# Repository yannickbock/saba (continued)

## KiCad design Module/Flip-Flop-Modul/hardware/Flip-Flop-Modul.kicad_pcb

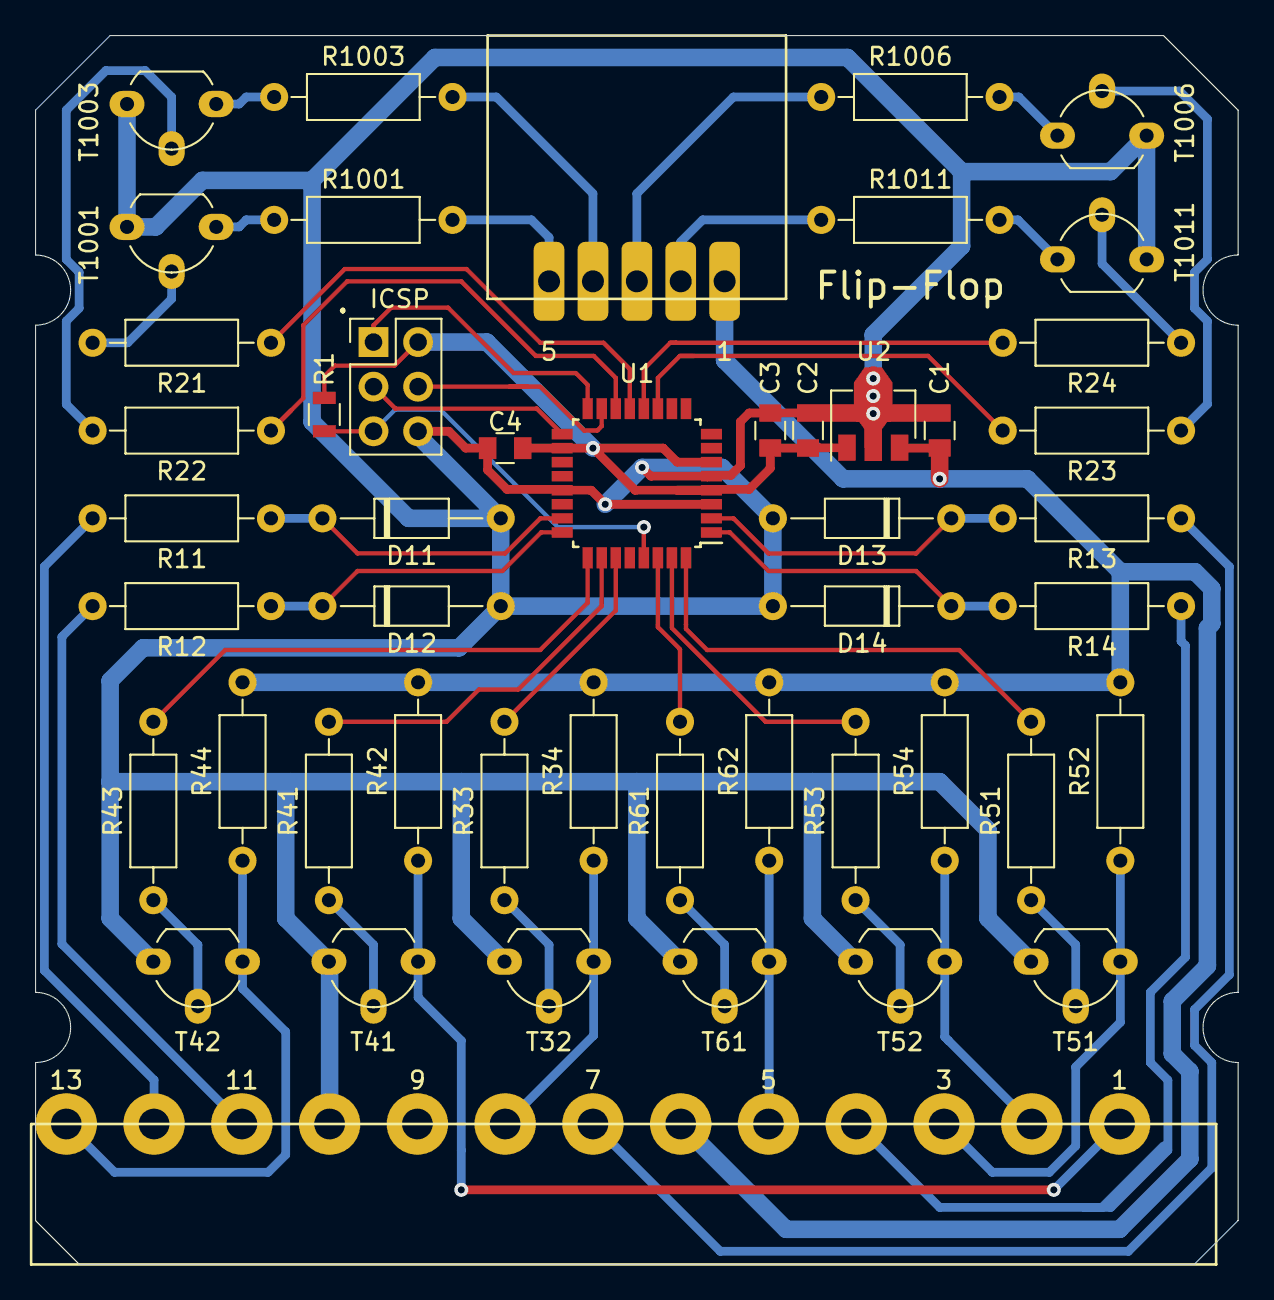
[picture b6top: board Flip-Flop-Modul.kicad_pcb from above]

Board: 2 copper layers, 68.5 x 70.0 mm, 48 parts (0 on the bottom side), 49 nets.

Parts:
C1, C2: 2.2µF; C_0805
C3, C4: 100nF; C_0805
D11, D12, D13, D14: 5V1; D_DO-35_SOD27_P10.16mm_Horizontal
J1: Conn_01x05; Connector_01x05_5mm_Stocko_Horizontal
J2: Conn_01x13; Connector_01x13_5mm
J3: ICSP; Pin_Header_Straight_2x03_Pitch2.54mm
R1: 10k; R_0805
R11, R12, R13, R14, R1001, R1003, R1006, R1011: 1k; R_Axial_DIN0207_L6.3mm_D2.5mm_P10.16mm_Horizontal
R21, R22, R23, R24, R33, R34, R41, R42, R43, R44, R51, R52, R53, R54, R61, R62: 10k; R_Axial_DIN0207_L6.3mm_D2.5mm_P10.16mm_Horizontal
T32, T41, T42, T51, T52, T61, T1001, T1003, T1006, T1011: BC547; TO-92_Molded_Wide_Oval
U1: ATmega8A-AU; LQFP-32_7x7mm_Pitch0.8mm
U2: LM78L05; SOT-89-3

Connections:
+5V: C2.1, C3.1, C4.1, J3.2, R1.1, U1.4, U1.6, U1.18, U2.1
+12V: C1.1, J1.1, J2.6, R34.2, R42.2, R44.2, R52.2, R54.2, R62.2, U2.3
GND: C1.2, C2.2, C3.2, C4.2, D11.2, D12.2, D13.2, D14.2, J2.10, J3.6, T32.3, T41.3, T42.3, T51.3, T52.3, T61.3, T1001.3, T1003.3, T1006.3, T1011.3, U1.3, U1.5, U1.21, U2.2
I1: J2.12, R11.1
I2: J2.11, R12.1
I3: J2.7, R13.1
I4: J2.4, R14.1
IN1: D11.1, R11.2, U1.23
IN2: D12.1, R12.2, U1.24
IN3: D13.1, R13.2, U1.2
IN4: D14.1, R14.2, U1.1
LED1: R21.2, U1.13
LED2: R22.2, U1.14
LED3: R23.2, U1.11
LED4: R24.2, U1.12
MISO: J3.1, U1.16
MOSI: J3.4, U1.15
NQ1: J2.8, R34.1, T32.1
NQ2: J2.13, R44.1, T42.1
NQ3: J2.2, R54.1, T52.1
unnamed: J1.2, R1011.1
unnamed: J1.3, R1006.1
unnamed: J1.4, R1003.1
unnamed: J1.5, R1001.1
unnamed: R21.1, T1001.2
unnamed: R22.1, T1003.2
unnamed: R23.1, T1006.2
unnamed: R24.1, T1011.2
unnamed: R33.1, T32.2
unnamed: R41.1, T41.2
unnamed: R43.1, T42.2
unnamed: R51.1, T51.2
unnamed: R53.1, T52.2
unnamed: R61.1, T61.2
unnamed: R1001.2, T1001.1
unnamed: R1003.2, T1003.1
unnamed: R1006.2, T1006.1
unnamed: R1011.2, T1011.1
OUT1N: R33.2, U1.27
OUT2: R41.2, U1.26
OUT2N: R43.2, U1.25
OUT3: R51.2, U1.32
OUT3N: R53.2, U1.31
OUT4: R61.2, U1.30
Q2: J2.1, R42.1, T41.1
Q3: J2.3, R52.1, T51.1
Q4: J2.5, R62.1, T61.1
RST: J3.5, R1.2, U1.29
SCK: J3.3, U1.17

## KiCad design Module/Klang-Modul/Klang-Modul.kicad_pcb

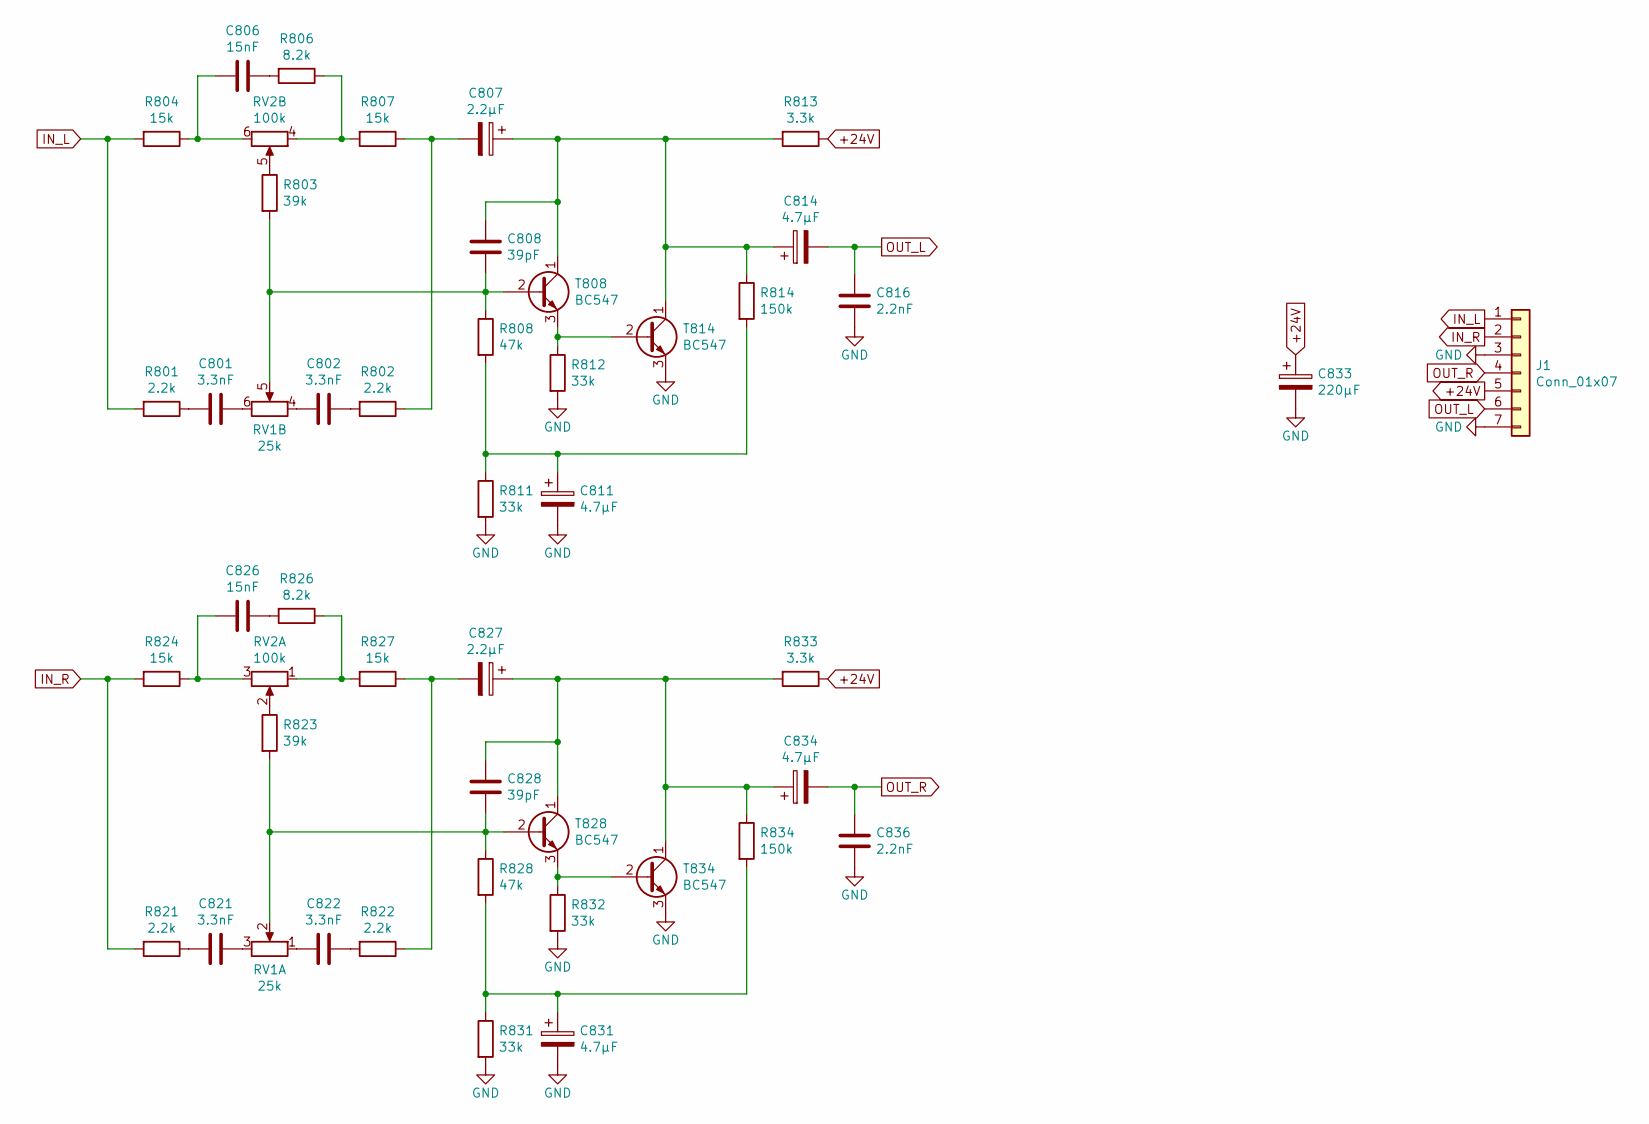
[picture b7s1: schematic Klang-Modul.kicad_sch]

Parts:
C801, C802, C821, C822: 3.3nF; C_Rect_L10.0mm_W3.0mm_P7.50mm_MKS4
C806, C826: 15nF; C_Rect_L10.0mm_W3.0mm_P7.50mm_MKS4
C807, C827: 2.2µF; C_Rect_L7.2mm_W7.2mm_P5.00mm_FKS2_FKP2_MKS2_MKP2
C808, C828: 39pF; C_Disc_D4.3mm_W1.9mm_P5.00mm
C811, C831: 4.7µF; CP_Radial_D5.0mm_P2.50mm
C814, C834: 4.7µF; C_Rect_L7.2mm_W7.2mm_P5.00mm_FKS2_FKP2_MKS2_MKP2
C816, C836: 2.2nF; C_Disc_D4.3mm_W1.9mm_P5.00mm
C833: 220µF; CP_Radial_D10.0mm_P5.00mm
J1: Conn_01x07
R801, R802, R821, R822: 2.2k; R_Axial_DIN0207_L6.3mm_D2.5mm_P10.16mm_Horizontal
R803, R823: 39k; R_Axial_DIN0207_L6.3mm_D2.5mm_P10.16mm_Horizontal
R804, R807, R824, R827: 15k; R_Axial_DIN0207_L6.3mm_D2.5mm_P10.16mm_Horizontal
R806, R826: 8.2k; R_Axial_DIN0207_L6.3mm_D2.5mm_P10.16mm_Horizontal
R808, R828: 47k; R_Axial_DIN0207_L6.3mm_D2.5mm_P10.16mm_Horizontal
R811, R812, R831, R832: 33k; R_Axial_DIN0207_L6.3mm_D2.5mm_P10.16mm_Horizontal
R813, R833: 3.3k; R_Axial_DIN0207_L6.3mm_D2.5mm_P10.16mm_Horizontal
R814, R834: 150k; R_Axial_DIN0207_L6.3mm_D2.5mm_P10.16mm_Horizontal
RV1: 25k; ALPS_xxxxBX2
RV2: 100k; ALPS_xxxxBX2
T808, T814, T828, T834: BC547; TO-92_Wide

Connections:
+24V: C833.1, J1.5, R813.1, R833.1
GND: C811.2, C816.2, C831.2, C833.2, C836.2, J1.3, J1.7, R811.2, R812.2, R831.2, R832.2, T814.3 (E), T834.3 (E)
IN_L: J1.1, R801.2, R804.2
IN_R: J1.2, R821.2, R824.2
unnamed: C801.1, RV1.6
unnamed: C801.2, R801.1
unnamed: C802.1, R802.2
unnamed: C802.2, RV1.4
unnamed: C806.1, R806.2
unnamed: C806.2, R804.1, RV2.6
unnamed: C807.2, R802.1, R807.1
unnamed: C811.1, R808.2, R811.1, R814.2
unnamed: C821.1, RV1.3
unnamed: C821.2, R821.1
unnamed: C822.1, R822.2
unnamed: C822.2, RV1.1
unnamed: C826.1, R826.2
unnamed: C826.2, R824.1, RV2.3
unnamed: C827.2, R822.1, R827.1
unnamed: C831.1, R828.2, R831.1, R834.2
unnamed: R803.1, RV2.5
unnamed: R806.1, R807.2, RV2.4
unnamed: R823.1, RV2.2
unnamed: R826.1, R827.2, RV2.1
unnamed: C808.2, R803.2, R808.1, RV1.5, T808.2 (B)
unnamed: C807.1, C808.1, C814.1, R813.2, R814.1, T808.1 (C), T814.1 (C)
unnamed: R812.1, T808.3 (E), T814.2 (B)
unnamed: C828.2, R823.2, R828.1, RV1.2, T828.2 (B)
unnamed: C827.1, C828.1, C834.1, R833.2, R834.1, T828.1 (C), T834.1 (C)
unnamed: R832.1, T828.3 (E), T834.2 (B)
OUT_L: C814.2, C816.1, J1.6
OUT_R: C834.2, C836.1, J1.4

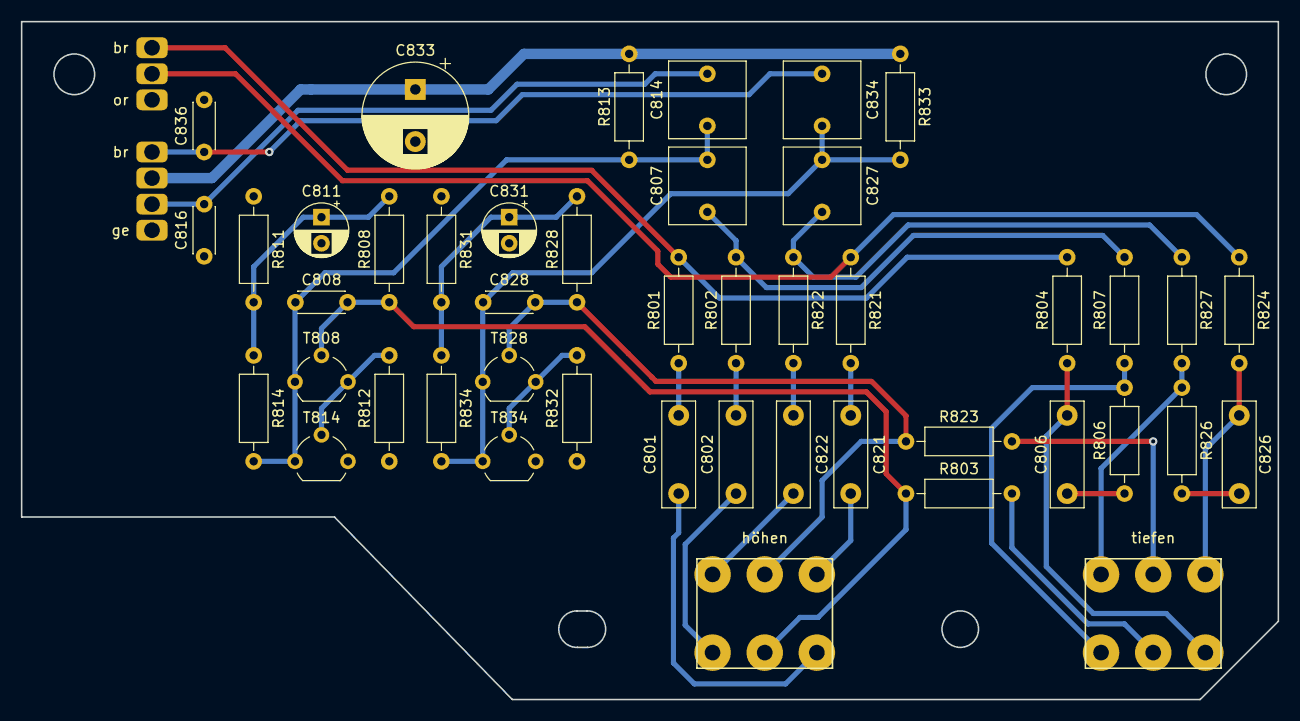
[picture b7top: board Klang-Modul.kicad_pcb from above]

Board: 2 copper layers, 120.5 x 65.0 mm, 46 parts (0 on the bottom side), 32 nets.

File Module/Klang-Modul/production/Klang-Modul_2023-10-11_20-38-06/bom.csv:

Designator,Footprint,Quantity,Value,LCSC Part #
"C801, C802, C821, C822",C_Rect_L10.0mm_W3.0mm_P7.50mm_MKS4,4,3.3nF,
"C806, C826",C_Rect_L10.0mm_W3.0mm_P7.50mm_MKS4,2,15nF,
"C807, C827",C_Rect_L7.2mm_W7.2mm_P5.00mm_FKS2_FKP2_MKS2_MKP2,2,2.2µF,
"C808, C828",C_Disc_D4.3mm_W1.9mm_P5.00mm,2,39pF,
"C811, C831",CP_Radial_D5.0mm_P2.50mm,2,4.7µF,
"C814, C834",C_Rect_L7.2mm_W7.2mm_P5.00mm_FKS2_FKP2_MKS2_MKP2,2,4.7µF,
"C816, C836",C_Disc_D4.3mm_W1.9mm_P5.00mm,2,2.2nF,
C833,CP_Radial_D10.0mm_P5.00mm,1,220µF,
J1,Conn_01x07,1,Conn_01x07,
"R801, R802, R821, R822",R_Axial_DIN0207_L6.3mm_D2.5mm_P10.16mm_Horizontal,4,2.2k,
"R803, R823",R_Axial_DIN0207_L6.3mm_D2.5mm_P10.16mm_Horizontal,2,39k,
"R804, R807, R824, R827",R_Axial_DIN0207_L6.3mm_D2.5mm_P10.16mm_Horizontal,4,15k,
"R806, R826",R_Axial_DIN0207_L6.3mm_D2.5mm_P10.16mm_Horizontal,2,8.2k,
"R808, R828",R_Axial_DIN0207_L6.3mm_D2.5mm_P10.16mm_Horizontal,2,47k,
"R811, R812, R831, R832",R_Axial_DIN0207_L6.3mm_D2.5mm_P10.16mm_Horizontal,4,33k,
"R813, R833",R_Axial_DIN0207_L6.3mm_D2.5mm_P10.16mm_Horizontal,2,3.3k,
"R814, R834",R_Axial_DIN0207_L6.3mm_D2.5mm_P10.16mm_Horizontal,2,150k,
RV1,ALPS_xxxxBX2,1,25k,
RV2,ALPS_xxxxBX2,1,100k,
"T808, T814, T828, T834",TO-92_Wide,4,BC547,
